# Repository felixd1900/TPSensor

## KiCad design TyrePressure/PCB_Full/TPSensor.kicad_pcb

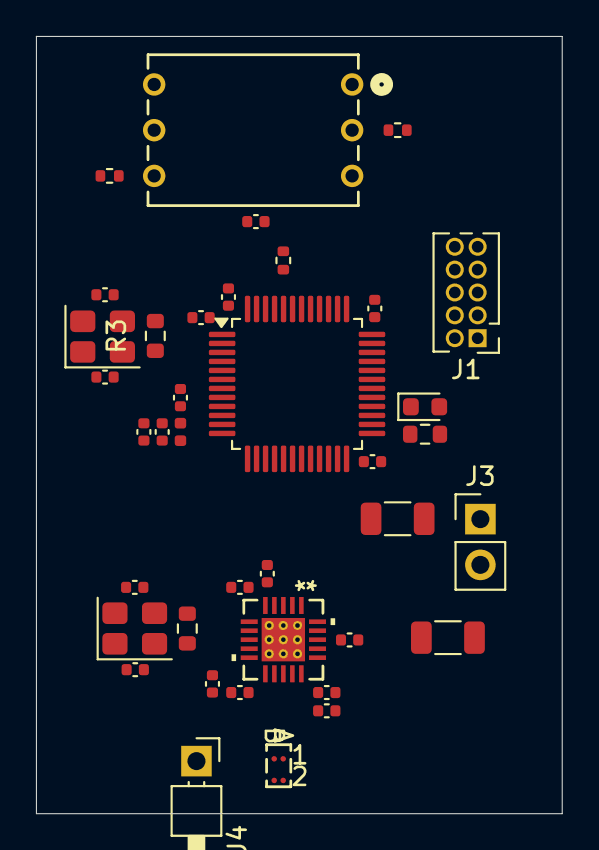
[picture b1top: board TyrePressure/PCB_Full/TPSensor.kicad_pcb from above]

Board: 4 copper layers, 29.2 x 43.2 mm, 38 parts (0 on the bottom side), 27 nets, no tracks yet.

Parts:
C1, C2, C3, C4, C6, C7, C8, C12, C14, C15, C18, C19, C51: 100nF; C_0402_1005Metric
C5, C16: 10uF; C_1206_3216Metric
C9, C17: 1uF; C_0402_1005Metric
C10, C11, C81, C101: 10pF; C_0402_1005Metric
D1: LED; LED_0603_1608Metric
J1: SWD_Connector; PinHeader_2x05_P1.27mm_Vertical
J3: Power_Connector; PinHeader_1x02_P2.54mm_Vertical
J4: Antenna_Connector; PinHeader_1x01_P2.54mm_Horizontal
L2: 39nH; L_0402_1005Metric
R2, R8, R9: 10k; R_0402_1005Metric
R3, R6: 47; R_0603_1608Metric
R4: 680; R_0603_1608Metric
U2: BAL-CC1101-01D3; BGA_01-01D3_STM
U3: CC1101RGPR; RGP20_2P4X2P4
U4: STM32L052C8Tx; LQFP-48_7x7mm_P0.5mm
U6: ABP2DANT001PG2A3XX; ABP2DANT&slash_G_HNW
Y1: 26MHz; Crystal_SMD_3225-4Pin_3.2x2.5mm
Y2: 16MHz; Crystal_SMD_3225-4Pin_3.2x2.5mm

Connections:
+3.3V: C1.1, C2.1, C3.1, C4.1, C5.1, C6.1, C7.1, C8.1, C12.1, C14.1, C15.1, C16.1, C19.1, J1.1, J3.2, L2.1, R8.1, R9.1, U3.4 (DVDD), U3.9 (AVDD), U3.11 (AVDD), U3.14 (AVDD), U3.15 (AVDD), U3.18 (DGUARD), U4.1 (VDD), U4.24 (VDD), U4.36 (VDD_USB), U4.48 (VDD), U6.1 (VDD)
/EOC: U4.41 (PB5), U6.3 (EOC)
/I2C_SCL: R8.2, U4.42 (PB6), U6.2 (SCL)
/I2C_SDA: R9.2, U4.43 (PB7), U6.4 (SDA)
/NRST: C9.1, J1.10, U4.7 (NRST)
/RF_Antenna: J4.1, U2.A1 (SE)
/RF_Received: U3.6 (GDO0), U4.13 (PA3)
/SPI_MISO: U3.2 (SO), U4.16 (PA6)
/SPI_MOSI: U3.20 (SI), U4.17 (PA7)
/SPI_NSS: U3.7 (CSN), U4.14 (PA4)
/SPI_SCK: U3.1 (SCLK), U4.15 (PA5)
/SWCLK: J1.4, U4.37 (PA14)
/SWDIO: J1.2, U4.34 (PA13)
/VDDA: C17.1, C18.1, L2.2, U4.9 (VDDA)
GND: C1.2, C2.2, C3.2, C4.2, C5.2, C6.2, C7.2, C8.2, C9.2, C10.2, C11.2, C12.2, C14.2, C15.2, C16.2, C17.2, C18.2, C19.2, C51.2, C81.2, C101.2, J1.3, J1.5, J1.9, J3.1, R2.2, R4.2, U2.B1 (GND), U3.16 (GND), U3.19 (GND), U3.21 (EPAD), U4.8 (VSSA), U4.23 (VSS), U4.35 (VSS), U4.47 (VSS), U6.5 (GND), Y1.2, Y1.4, Y2.2, Y2.4
unnamed: C10.1, R3.2, Y2.3
unnamed: C101.1, R6.2, Y1.3
unnamed: D1.2 (A), U4.28 (PB15)
unnamed: D1.1 (K), R4.1
unnamed: U2.A2 (DIFF), U3.13 (RF_N)
unnamed: U2.B2 (DIFF), U3.12 (RF_P)
unnamed: R6.1, U3.8 (XOSC_Q1)
unnamed: C81.1, U3.10 (XOSC_Q2), Y1.1
unnamed: C51.1, U3.5 (DCOUPL)
unnamed: R2.1, U4.44 (BOOT0)
unnamed: C11.1, U4.5 (PH0), Y2.1
unnamed: R3.1, U4.6 (PH1)

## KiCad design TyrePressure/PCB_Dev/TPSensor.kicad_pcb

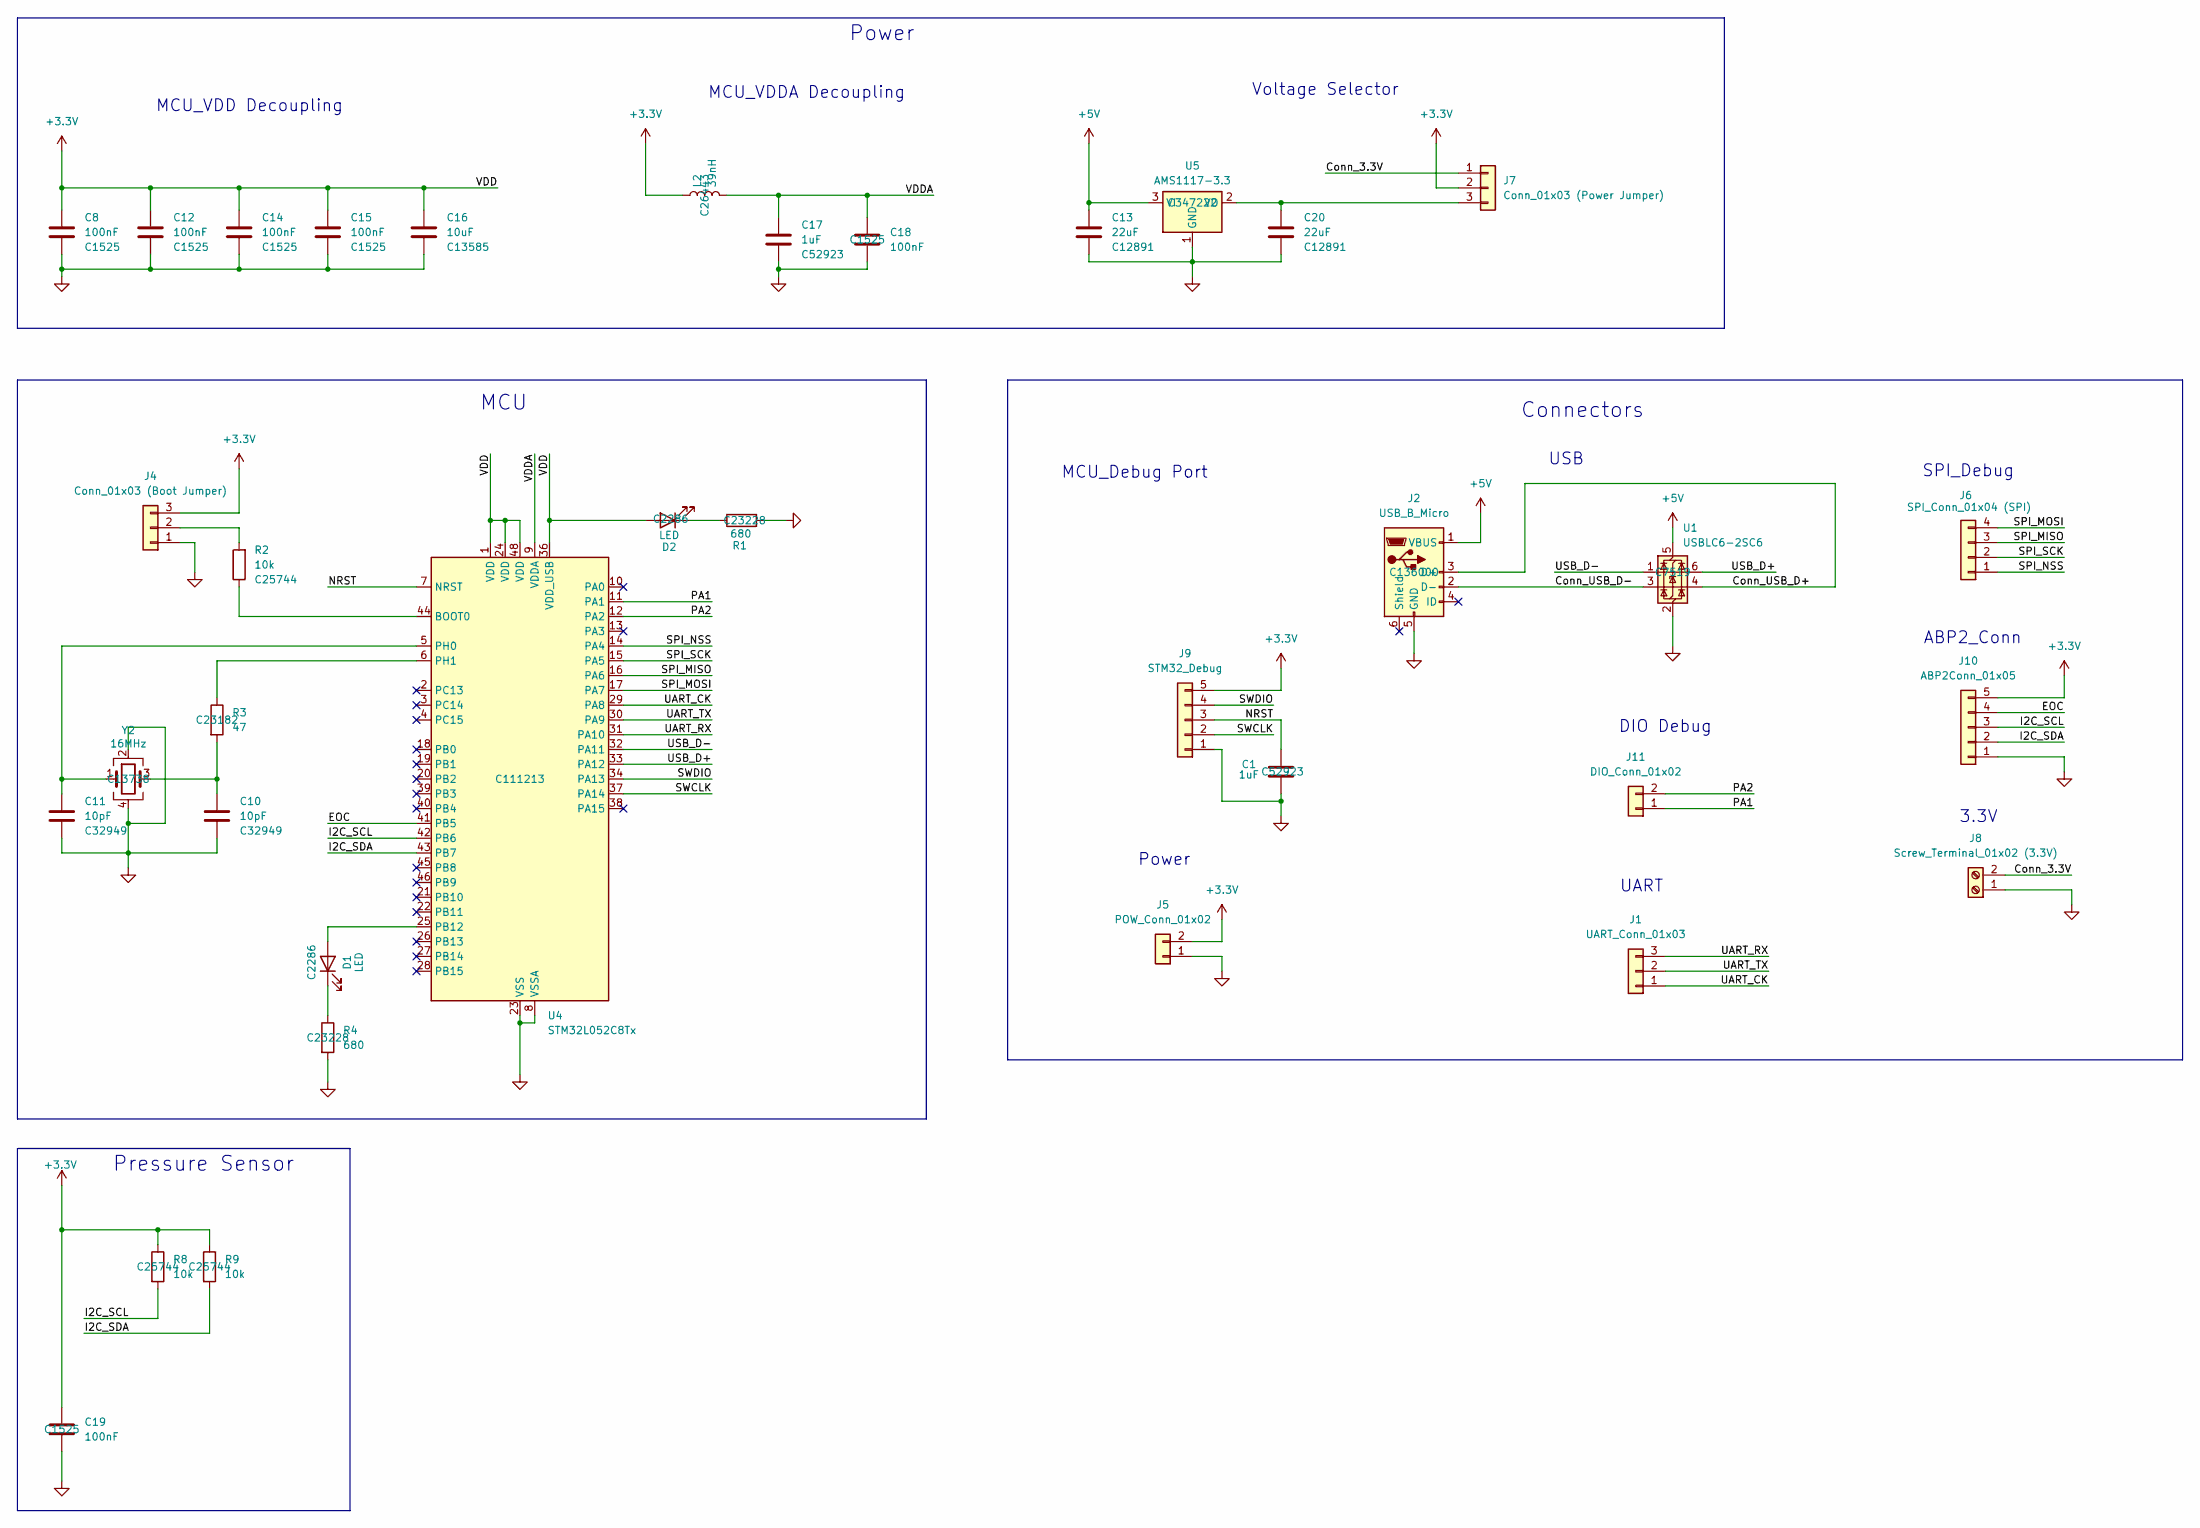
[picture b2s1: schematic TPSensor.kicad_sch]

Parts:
C1, C17: 1uF; C_0402_1005Metric; LCSC C52923
C8, C12, C14, C15, C18, C19: 100nF; C_0402_1005Metric; LCSC C1525
C10, C11: 10pF; C_0402_1005Metric; LCSC C32949
C13, C20: 22uF; C_1206_3216Metric; LCSC C12891
C16: 10uF; C_1206_3216Metric; LCSC C13585
D1, D2: LED; LED_0603_1608Metric; LCSC C2286
J1: UART_Conn_01x03; PinHeader_1x03_P2.54mm_Vertical
J2: USB_B_Micro; USB_Micro-B_Molex-105017-0001; LCSC C136000
J4: Conn_01x03 (Boot Jumper); PinHeader_1x03_P2.54mm_Vertical
J5: POW_Conn_01x02; PinHeader_1x02_P2.54mm_Vertical
J6: SPI_Conn_01x04 (SPI); PinHeader_1x04_P2.54mm_Vertical
J7: Conn_01x03 (Power Jumper); PinHeader_1x03_P2.54mm_Vertical
J8: Screw_Terminal_01x02 (3.3V); TerminalBlock_Phoenix_MKDS-3-2-5.08_1x02_P5.08mm_Horizontal
J9: STM32_Debug; PinHeader_1x05_P2.54mm_Vertical
J10: ABP2Conn_01x05; PinHeader_1x05_P2.54mm_Vertical
J11: DIO_Conn_01x02; PinHeader_1x02_P2.54mm_Vertical
L2: 39nH; L_0402_1005Metric; LCSC C26443
R1, R4: 680; R_0603_1608Metric; LCSC C23228
R2, R8, R9: 10k; R_0402_1005Metric; LCSC C25744
R3: 47; R_0603_1608Metric; LCSC C23182
U1: USBLC6-2SC6; SOT-23-6; LCSC C7519
U4: STM32L052C8Tx; LQFP-48_7x7mm_P0.5mm; LCSC C111213
U5: AMS1117-3.3; SOT-223; LCSC C347222
Y2: 16MHz; Crystal_SMD_3225-4Pin_3.2x2.5mm; LCSC C13738

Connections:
+3.3V: C8.1, C12.1, C14.1, C15.1, C16.1, C19.1, D2.2 (A), J4.3, J5.2, J7.2, J9.5, J10.5, L2.1, R8.1, R9.1, U4.1 (VDD), U4.24 (VDD), U4.36 (VDD_USB), U4.48 (VDD)
+5V: C13.1, J2.1 (VBUS), U1.5 (VBUS), U5.3 (VI)
/Conn_3.3V: J7.1, J8.2
/Conn_USB_D+: J2.3 (D+), U1.4 (I/O2)
/Conn_USB_D-: J2.2 (D-), U1.3 (I/O2)
/EOC: J10.4, U4.41 (PB5)
/I2C_SCL: J10.3, R8.2, U4.42 (PB6)
/I2C_SDA: J10.2, R9.2, U4.43 (PB7)
/NRST: C1.1, J9.3, U4.7 (NRST)
/PA1: J11.1, U4.11 (PA1)
/PA2: J11.2, U4.12 (PA2)
/SPI_MISO: J6.3, U4.16 (PA6)
/SPI_MOSI: J6.4, U4.17 (PA7)
/SPI_NSS: J6.1, U4.14 (PA4)
/SPI_SCK: J6.2, U4.15 (PA5)
/SWCLK: J9.2, U4.37 (PA14)
/SWDIO: J9.4, U4.34 (PA13)
/UART_CK: J1.1, U4.29 (PA8)
/UART_RX: J1.3, U4.31 (PA10)
/UART_TX: J1.2, U4.30 (PA9)
/USB_D+: U1.6 (I/O1), U4.33 (PA12)
/USB_D-: U1.1 (I/O1), U4.32 (PA11)
/VDDA: C17.1, C18.1, L2.2, U4.9 (VDDA)
GND: C1.2, C8.2, C10.2, C11.2, C12.2, C13.2, C14.2, C15.2, C16.2, C17.2, C18.2, C19.2, C20.2, J2.5 (GND), J4.1, J5.1, J8.1, J9.1, J10.1, R1.2, R4.2, U1.2 (GND), U4.8 (VSSA), U4.23 (VSS), U4.35 (VSS), U4.47 (VSS), U5.1 (GND), Y2.2, Y2.4
unnamed: C10.1, R3.2, Y2.3
unnamed: D1.2 (A), U4.25 (PB12)
unnamed: D1.1 (K), R4.1
unnamed: D2.1 (K), R1.1
unnamed: J4.2, R2.2
unnamed: C20.1, J7.3, U5.2 (VO)
unnamed: R2.1, U4.44 (BOOT0)
unnamed: C11.1, U4.5 (PH0), Y2.1
unnamed: R3.1, U4.6 (PH1)

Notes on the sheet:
3.3V
MCU_VDDA Decoupling
ABP2_Conn
UART
DIO Debug
Voltage Selector
SPI_Debug
MCU_VDD Decoupling
Power
MCU
Pressure Sensor
Connectors
USB
MCU_Debug Port

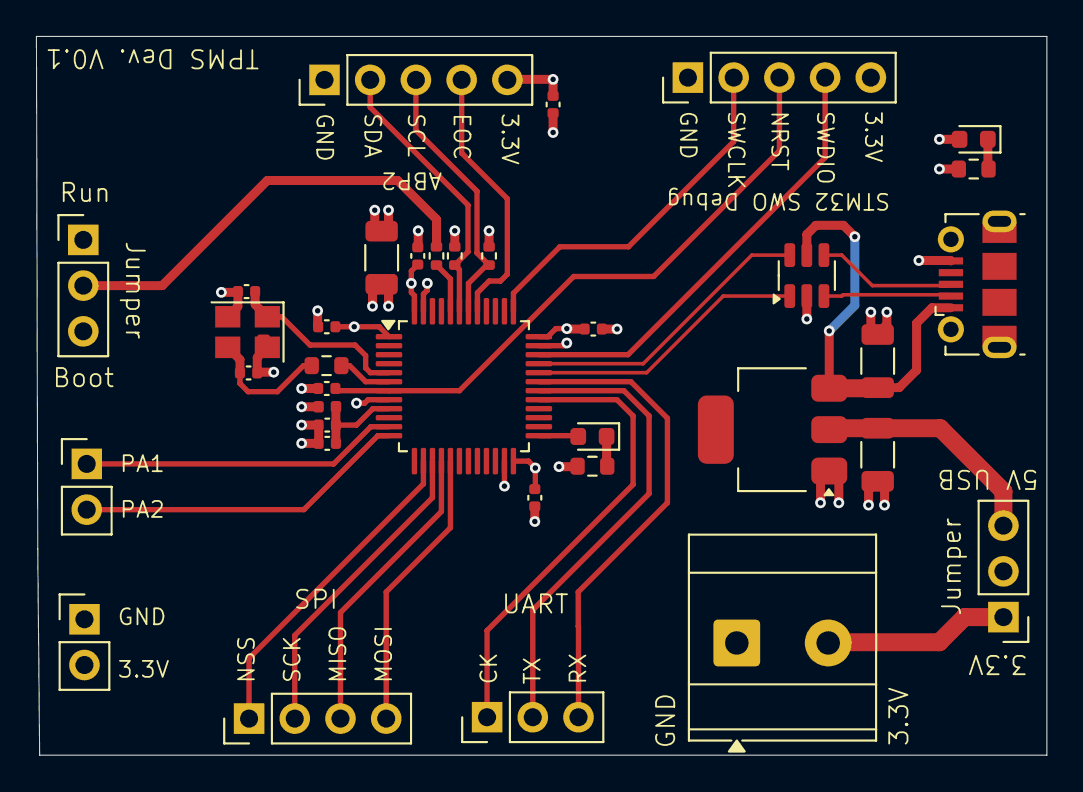
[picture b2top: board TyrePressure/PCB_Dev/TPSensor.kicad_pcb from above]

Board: 4 copper layers, 56.1 x 39.9 mm, 36 parts (0 on the bottom side), 33 nets.

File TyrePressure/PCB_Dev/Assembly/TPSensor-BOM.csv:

"Comment","Designator","Footprint","LCSC"
"1uF","C1","Capacitor_SMD:C_0402_1005Metric","C52923"
"100nF","C8","Capacitor_SMD:C_0402_1005Metric","C1525"
"10pF","C10","Capacitor_SMD:C_0402_1005Metric","C32949"
"10pF","C11","Capacitor_SMD:C_0402_1005Metric","C32949"
"100nF","C12","Capacitor_SMD:C_0402_1005Metric","C1525"
"22uF","C13","Capacitor_SMD:C_1206_3216Metric","C12891"
"100nF","C14","Capacitor_SMD:C_0402_1005Metric","C1525"
"100nF","C15","Capacitor_SMD:C_0402_1005Metric","C1525"
"10uF","C16","Capacitor_SMD:C_1206_3216Metric","C13585"
"1uF","C17","Capacitor_SMD:C_0402_1005Metric","C52923"
"100nF","C18","Capacitor_SMD:C_0402_1005Metric","C1525"
"100nF","C19","Capacitor_SMD:C_0402_1005Metric","C1525"
"22uF","C20","Capacitor_SMD:C_1206_3216Metric","C12891"
"LED","D1","LED_SMD:LED_0603_1608Metric","C2286"
"LED","D2","LED_SMD:LED_0603_1608Metric","C2286"
"UART_Conn_01x03","J1","Connector_PinHeader_2.54mm:PinHeader_1x03_P2.54mm_Vertical",""
"USB_B_Micro","J2","Connector_USB:USB_Micro-B_Molex-105017-0001","C136000"
"Conn_01x03 (Boot Jumper)","J4","Connector_PinHeader_2.54mm:PinHeader_1x03_P2.54mm_Vertical",""
"POW_Conn_01x02","J5","Connector_PinHeader_2.54mm:PinHeader_1x02_P2.54mm_Vertical",""
"SPI_Conn_01x04 (SPI)","J6","Connector_PinHeader_2.54mm:PinHeader_1x04_P2.54mm_Vertical",""
"Conn_01x03 (Power Jumper)","J7","Connector_PinHeader_2.54mm:PinHeader_1x03_P2.54mm_Vertical",""
"Screw_Terminal_01x02 (3.3V)","J8","TerminalBlock_Phoenix:TerminalBlock_Phoenix_MKDS-3-2-5.08_1x02_P5.08mm_Horizontal",""
"STM32_Debug","J9","Connector_PinHeader_2.54mm:PinHeader_1x05_P2.54mm_Vertical",""
"ABP2Conn_01x05","J10","Connector_PinHeader_2.54mm:PinHeader_1x05_P2.54mm_Vertical",""
"DIO_Conn_01x02","J11","Connector_PinHeader_2.54mm:PinHeader_1x02_P2.54mm_Vertical",""
"39nH","L2","Inductor_SMD:L_0402_1005Metric","C26443"
"680","R1","Resistor_SMD:R_0603_1608Metric","C23228"
"10k","R2","Resistor_SMD:R_0402_1005Metric","C25744"
"47","R3","Resistor_SMD:R_0603_1608Metric","C23182"
"680","R4","Resistor_SMD:R_0603_1608Metric","C23228"
"10k","R8","Resistor_SMD:R_0402_1005Metric","C25744"
"10k","R9","Resistor_SMD:R_0402_1005Metric","C25744"
"USBLC6-2SC6","U1","Package_TO_SOT_SMD:SOT-23-6","C7519"
"STM32L052C8Tx","U4","Package_QFP:LQFP-48_7x7mm_P0.5mm","C111213"
"AMS1117-3.3","U5","Package_TO_SOT_SMD:SOT-223","C347222"
"16MHz","Y2","Crystal:Crystal_SMD_3225-4Pin_3.2x2.5mm","C13738"

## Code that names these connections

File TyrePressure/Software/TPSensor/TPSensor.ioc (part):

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Mcu.Name=STM32L052C(6-8)Tx
Mcu.Package=LQFP48
Mcu.UserName=STM32L052C8Tx
PA1.GPIOParameters=GPIO_PuPd,GPIO_Label,GPIO_ModeDefaultEXTI
PA1.GPIO_Label=RX_IRQ
PA1.GPIO_ModeDefaultEXTI=GPIO_MODE_IT_FALLING
PA1.GPIO_PuPd=GPIO_PULLDOWN
PA1.Signal=GPXTI1
PA13.Mode=Serial_Wire
PA13.Signal=SYS_SWDIO
PA14.Mode=Serial_Wire
PA14.Signal=SYS_SWCLK
PA2.GPIOParameters=GPIO_PuPd,GPIO_Label,GPIO_ModeDefaultEXTI
PA2.GPIO_Label=RX_TX_SW_IRQ
PA2.GPIO_ModeDefaultEXTI=GPIO_MODE_IT_RISING_FALLING
PA2.GPIO_PuPd=GPIO_PULLDOWN
PA2.Signal=GPXTI2
PA4.GPIOParameters=GPIO_Speed,GPIO_Label
PA4.GPIO_Label=SPI1_CS
PA4.GPIO_Speed=GPIO_SPEED_FREQ_HIGH
PA4.Signal=GPIO_Output
PA5.Mode=Full_Duplex_Master
PA5.Signal=SPI1_SCK
PA6.Mode=Full_Duplex_Master
PA6.Signal=SPI1_MISO
PA7.Mode=Full_Duplex_Master
PA7.Signal=SPI1_MOSI
PB12.GPIOParameters=GPIO_Label
PB12.GPIO_Label=Debug_LED
PB12.Signal=GPIO_Output
PB13.Signal=S_TIM21_CH1
PB4.Signal=S_TIM22_CH1
PB5.GPIOParameters=GPIO_Label
PB5.GPIO_Label=ABP2_EOC
PB5.Signal=GPIO_Input
PB6.Mode=I2C
PB6.Signal=I2C1_SCL
PB7.Mode=I2C
PB7.Signal=I2C1_SDA
PH0-OSC_IN.Mode=HSE-External-Oscillator
PH0-OSC_IN.Signal=RCC_OSC_IN
PH1-OSC_OUT.Mode=HSE-External-Oscillator
PH1-OSC_OUT.Signal=RCC_OSC_OUT
RCC.HSE_VALUE=16000000
RCC.SYSCLKFreq_VALUE=32000000
RCC.SYSCLKSource=RCC_SYSCLKSOURCE_PLLCLK
board=custom

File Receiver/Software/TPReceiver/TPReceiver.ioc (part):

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Mcu.Name=STM32L052C(6-8)Tx
Mcu.Package=LQFP48
Mcu.UserName=STM32L052C8Tx
PA1.GPIOParameters=GPIO_PuPd,GPIO_Label,GPIO_ModeDefaultEXTI
PA1.GPIO_Label=RX_IRQ
PA1.GPIO_ModeDefaultEXTI=GPIO_MODE_IT_FALLING
PA1.GPIO_PuPd=GPIO_PULLDOWN
PA1.Signal=GPXTI1
PA11.Mode=Device
PA11.Signal=USB_DM
PA12.Mode=Device
PA12.Signal=USB_DP
PA13.Mode=Serial_Wire
PA13.Signal=SYS_SWDIO
PA14.Mode=Serial_Wire
PA14.Signal=SYS_SWCLK
PA2.Signal=S_TIM21_CH1
PA4.GPIOParameters=GPIO_Label
PA4.GPIO_Label=SPI1_CS
PA4.Signal=GPIO_Output
PA5.Mode=Full_Duplex_Master
PA5.Signal=SPI1_SCK
PA6.Mode=Full_Duplex_Master
PA6.Signal=SPI1_MISO
PA7.Mode=Full_Duplex_Master
PA7.Signal=SPI1_MOSI
PB12.GPIOParameters=GPIO_Label
PB12.GPIO_Label=Debug_LED
PB12.Signal=GPIO_Output
PH0-OSC_IN.Mode=HSE-External-Oscillator
PH0-OSC_IN.Signal=RCC_OSC_IN
PH1-OSC_OUT.Mode=HSE-External-Oscillator
PH1-OSC_OUT.Signal=RCC_OSC_OUT
RCC.HSE_VALUE=16000000
RCC.SYSCLKFreq_VALUE=32000000
RCC.SYSCLKSource=RCC_SYSCLKSOURCE_PLLCLK
board=custom

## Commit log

2025-08-17 added stm32 project
2025-08-27 added close range issues documentation
2025-08-27 power changes
